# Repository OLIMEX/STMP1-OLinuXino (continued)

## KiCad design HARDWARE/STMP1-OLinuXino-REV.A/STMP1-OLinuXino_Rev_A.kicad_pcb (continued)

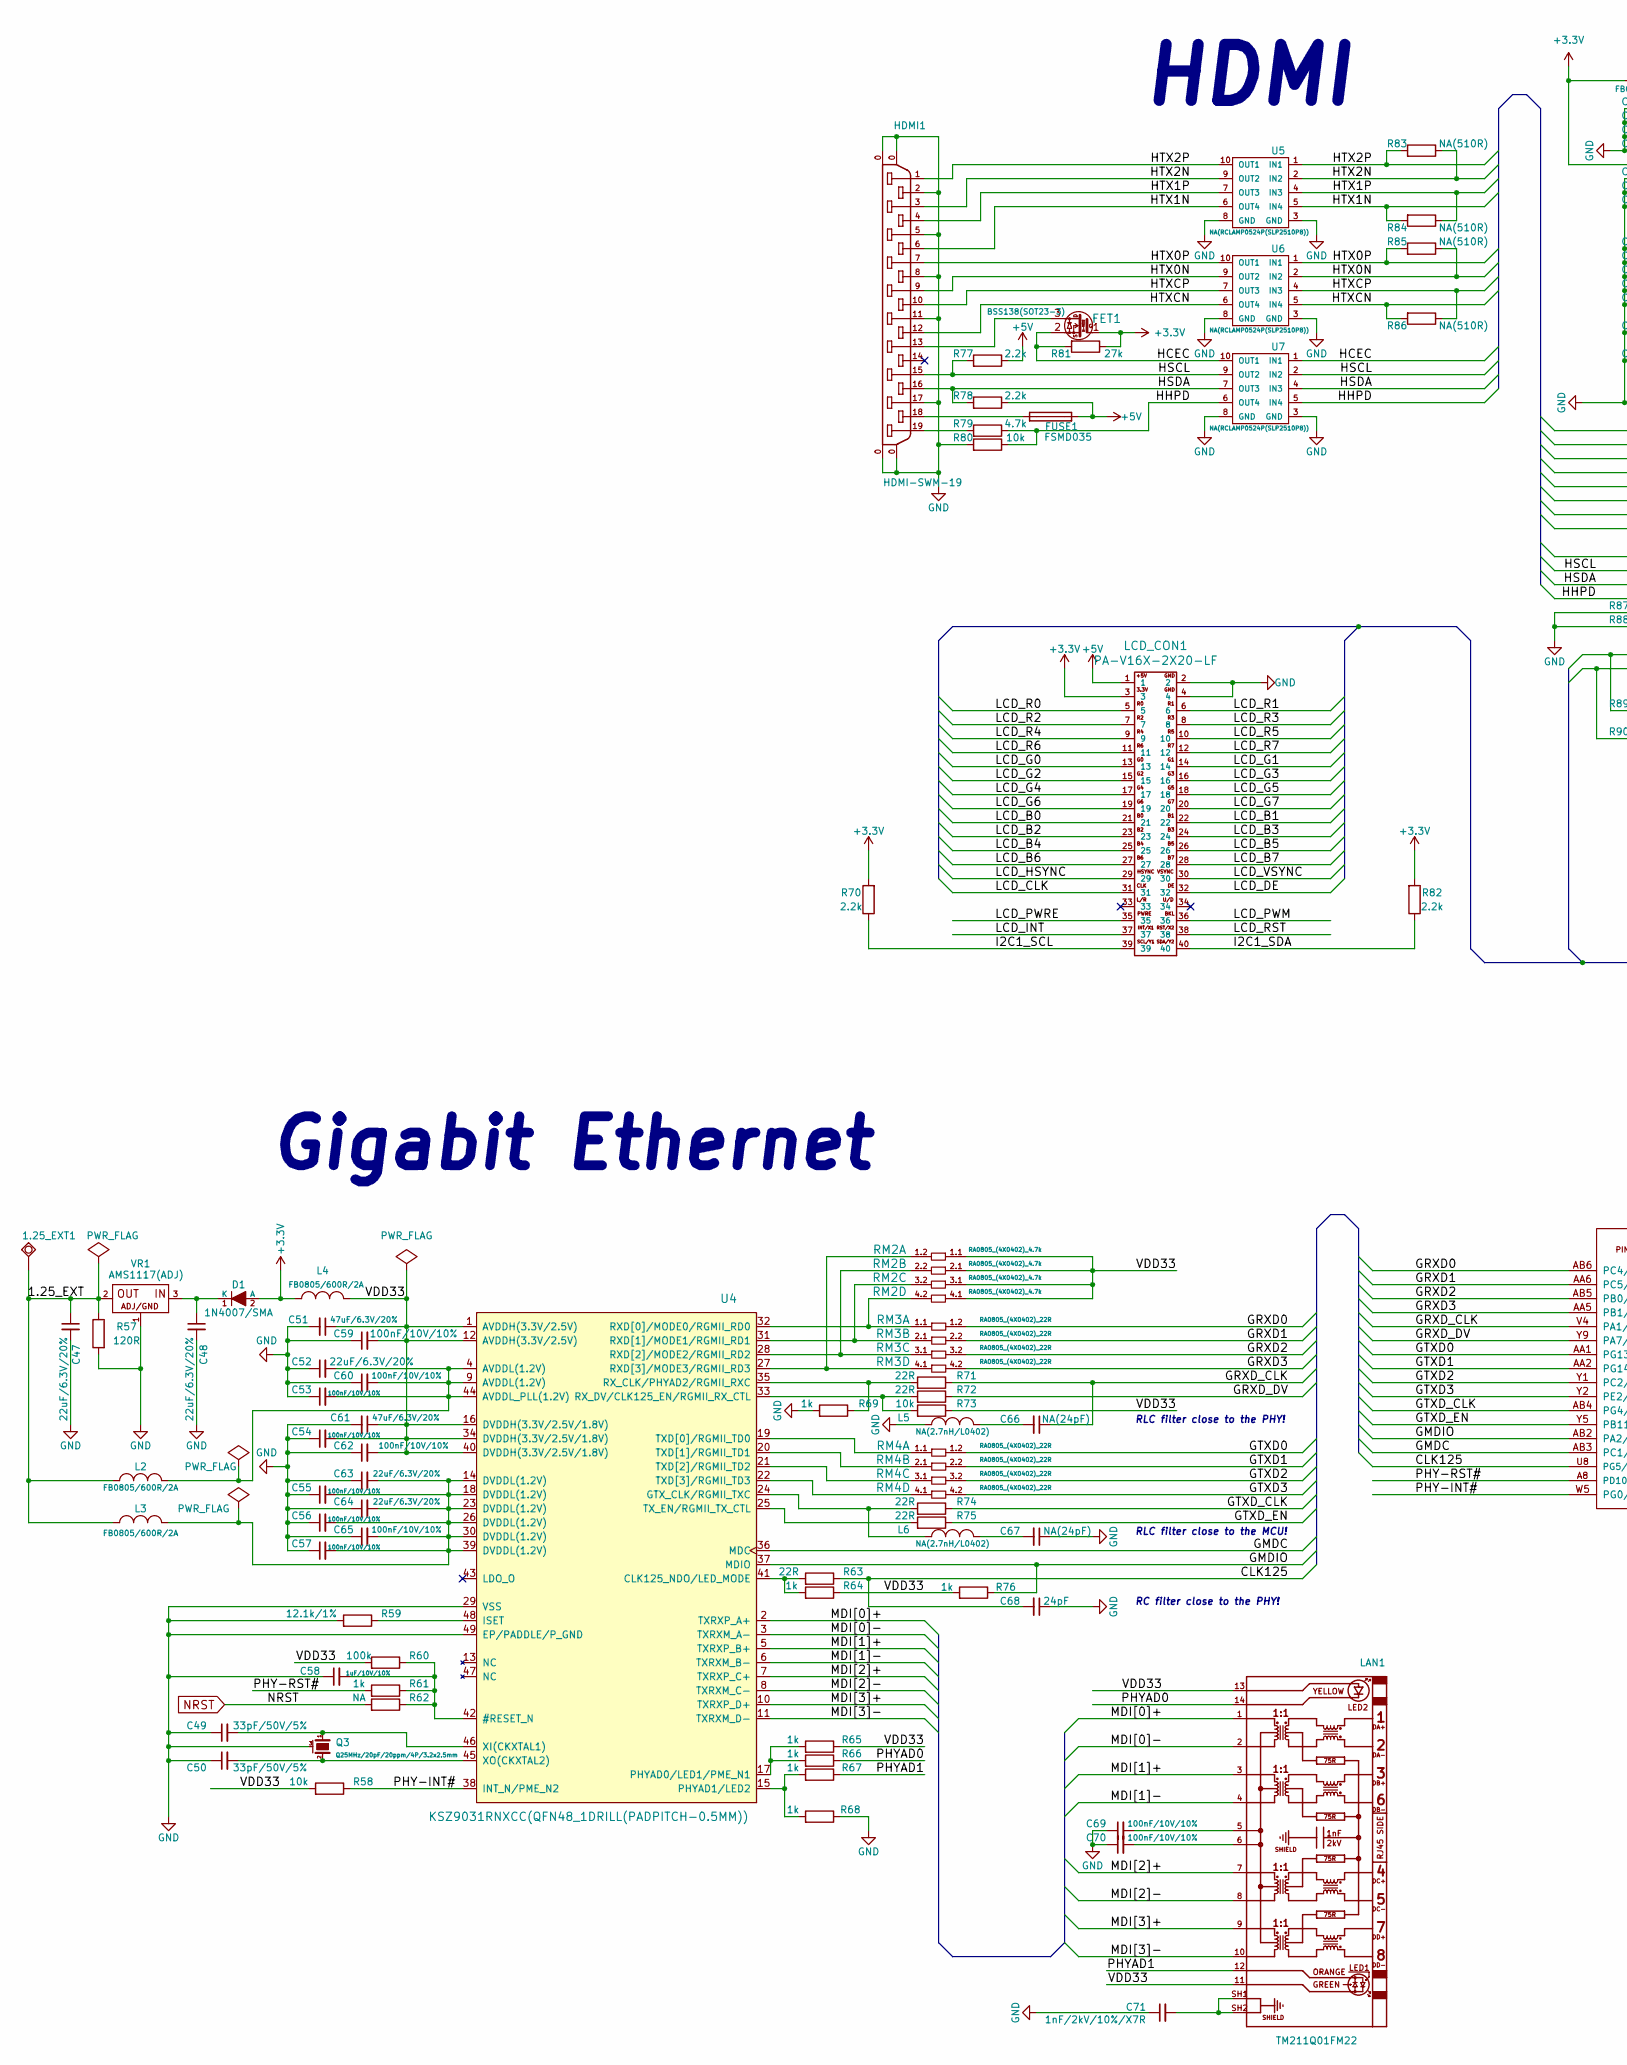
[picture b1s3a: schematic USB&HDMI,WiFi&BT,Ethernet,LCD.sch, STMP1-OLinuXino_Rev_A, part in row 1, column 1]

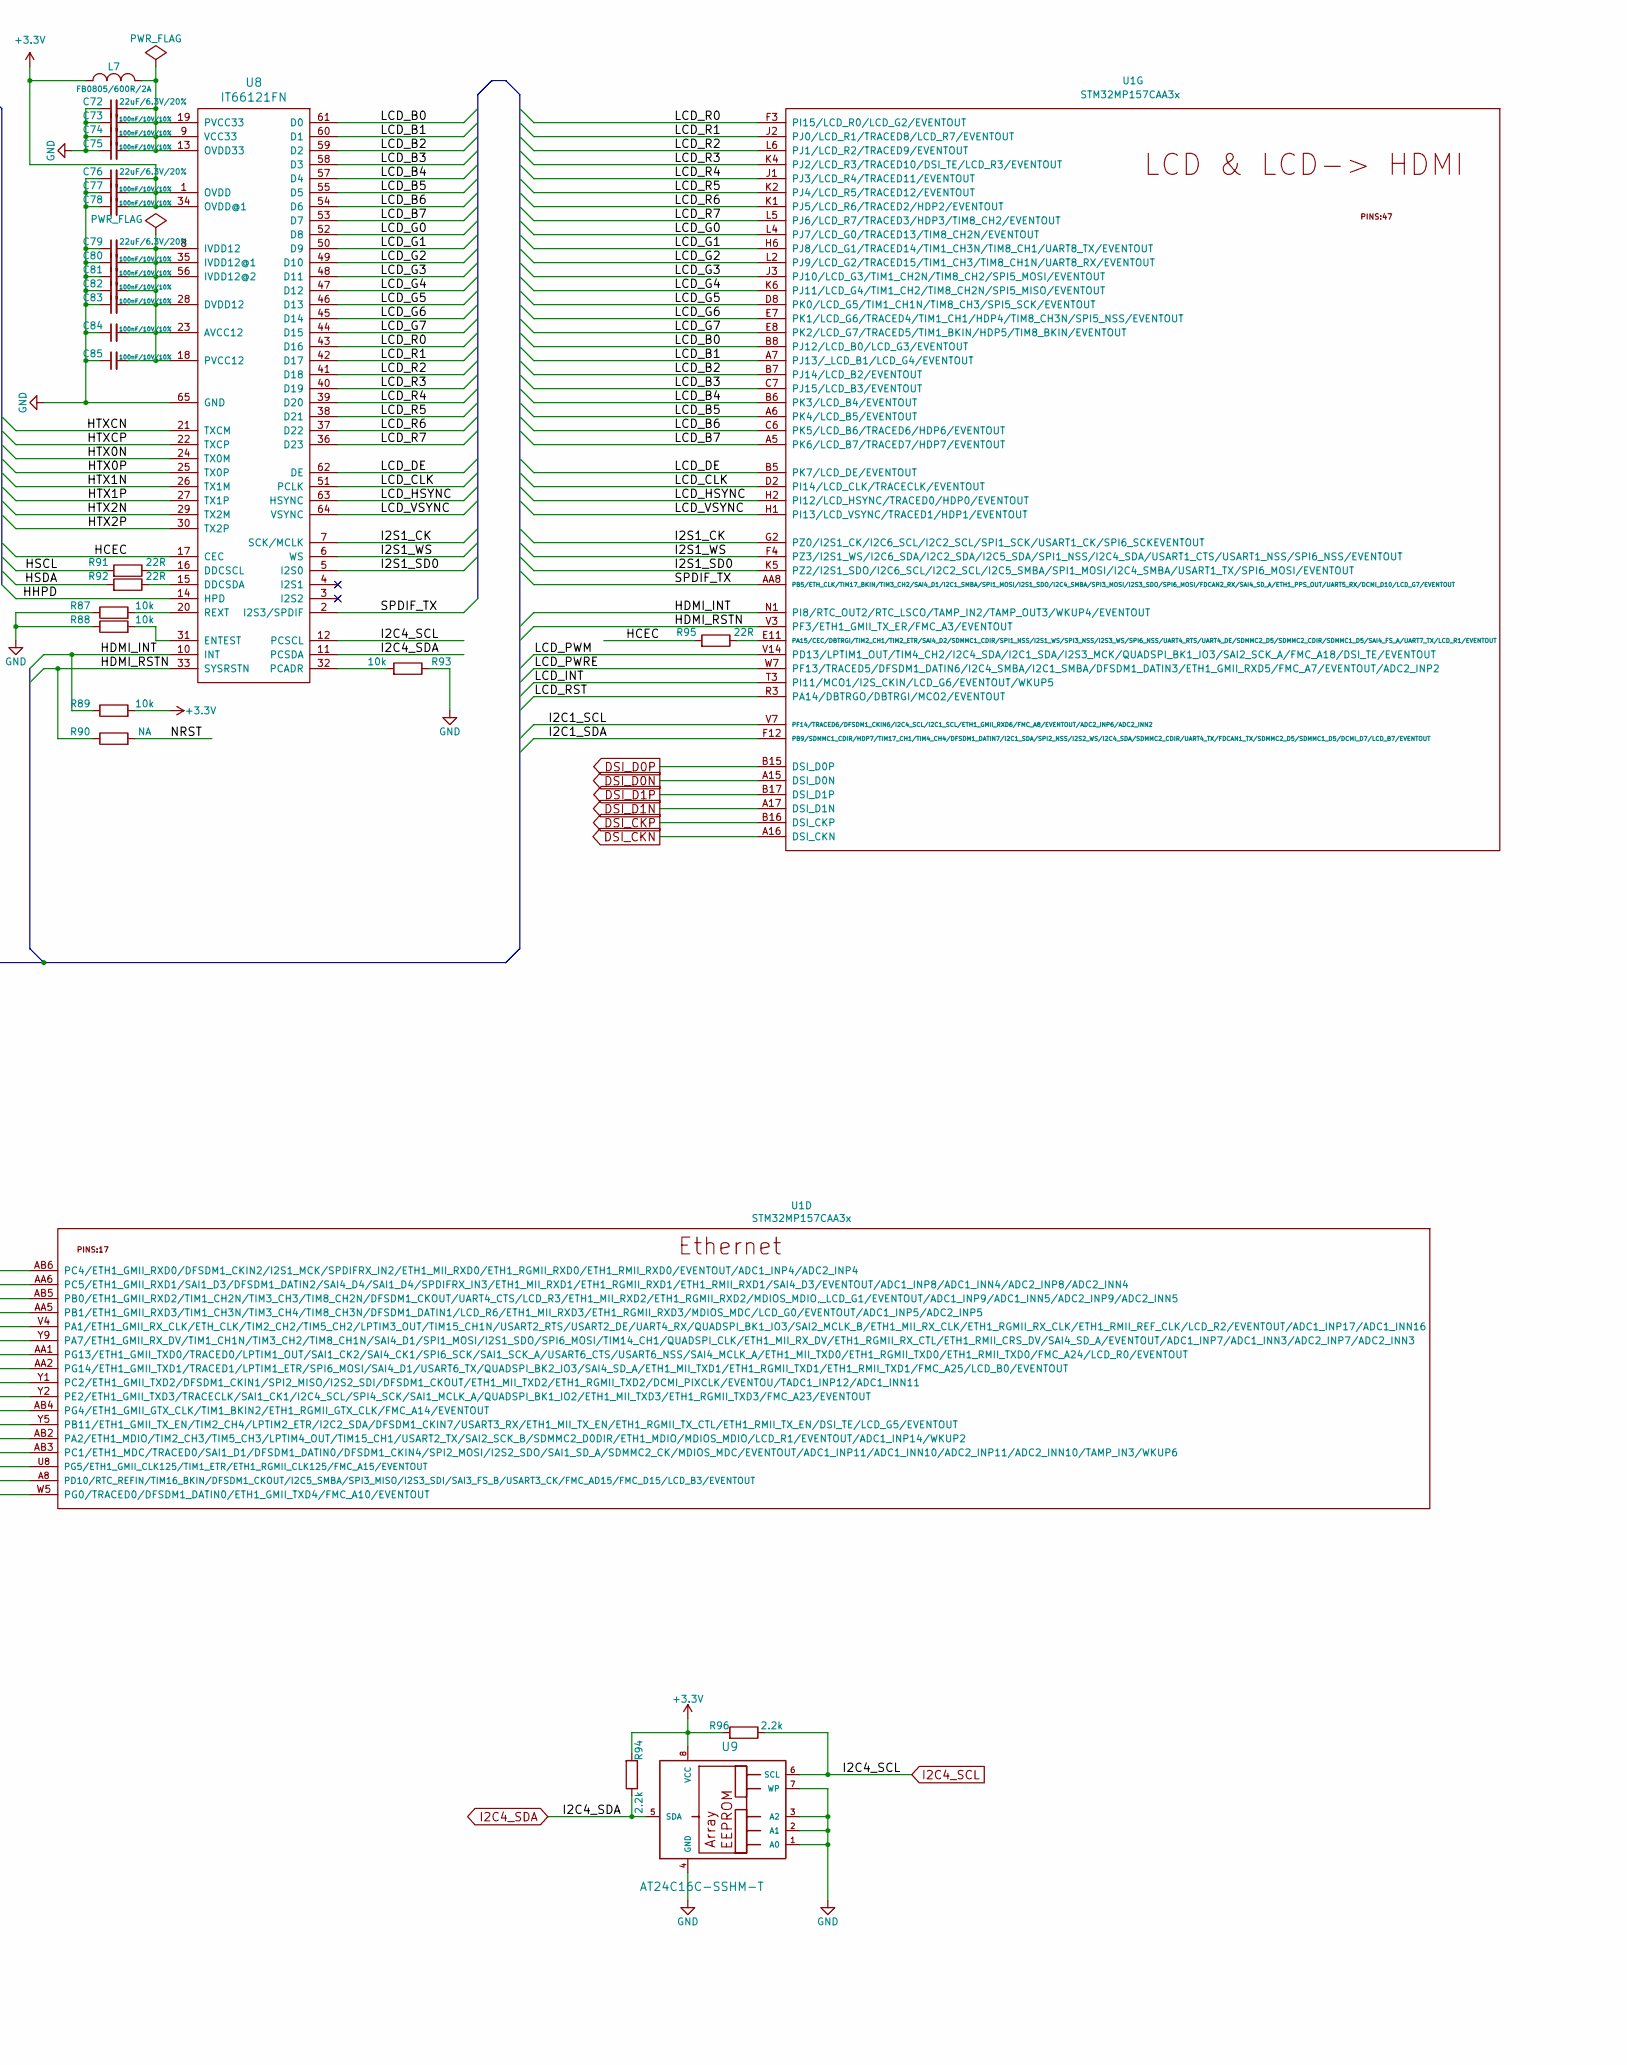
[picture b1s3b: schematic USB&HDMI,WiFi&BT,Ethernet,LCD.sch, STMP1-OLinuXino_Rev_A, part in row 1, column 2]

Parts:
1.25_EXT1: TESTPAD; TP_SMD
C47, C48, C52, C63, C64, C72, C76, C79: 22uF/6.3V/20%; C_0603_5MIL_DWS
C49, C50: 33pF/50V/5%; C_0402_5MIL_DWS
C51, C61: 47uF/6.3V/20%; C_0805_5MIL_DWS
C53, C54, C55, C56, C57, C59, C60, C62, C65, C69, C70, C73, C74, C75, C77, C78, C80, C81, C82, C83, C84, C85: 100nF/10V/10%; C_0402_5MIL_DWS
C58: 1uF/10V/10%; C_0603_5MIL_DWS
C66, C67: NA(24pF); C_0402_5MIL_DWS
C68: 24pF; C_0402_5MIL_DWS
C71: 1nF/2kV/10%/X7R; C_1206_5MIL_DWS_ISO
D1: 1N4007/SMA; SMA-KA
FET1: BSS138(SOT23-3); SOT23
FUSE1: FSMD035; FUSE-1206
HDMI1: HDMI-SWM-19
L2, L3, L4, L7: FB0805/600R/2A; L_0805_5MIL_DWS
L5, L6: NA(2.7nH/L0402); L_0402_5MIL_DWS
LAN1: TM211Q01FM22
LCD_CON1: PA-V16X-2X20-LF; GPH127SMT-02X20(PA-V16X-2X20-LF)
Q3: Q25MHz/20pF/20ppm/4P/3.2x2.5mm; TSX-3.2x2.5mm_GND(3)
R57: 120R; R_0603_5MIL_DWS
R58, R73, R80, R87, R88, R89, R93: 10k; R_0402_5MIL_DWS
R59: 12.1k/1%; R_0603_5MIL_DWS
R60: 100k; R_0402_5MIL_DWS
R61, R64, R65, R66, R67, R68, R69, R76: 1k; R_0402_5MIL_DWS
R62, R90: NA; R_0402_5MIL_DWS
R63, R71, R72, R74, R75, R91, R92, R95: 22R; R_0402_5MIL_DWS
R70, R77, R78, R82, R94, R96: 2.2k; R_0402_5MIL_DWS
R79: 4.7k; R_0402_5MIL_DWS
R81: 27k; R_0402_5MIL_DWS
R83, R84, R85, R86: NA(510R); R_0402_5MIL_DWS
RM2: RA0805_(4X0402)_4.7k; RA0805_(4X0402)_xx_BIGGEROUTPADS
RM3, RM4: RA0805_(4X0402)_22R; RA0805_(4X0402)_xx_BIGGEROUTPADS
U1: STM32MP157CAA3x; LFBGA-448(Pitch-0.8mm_Pad-0.4mm_18x18x1.27mm)
U4: KSZ9031RNXCC(QFN48_1DRILL(PADPITCH-0.5MM)); QFN48_1DRILL(PADPITCH-0.5MM)
U5, U6, U7: NA(RCLAMP0524P(SLP2510P8)); SLP2510P8_TEST
U8: IT66121FN; QFN64_9x9mm_Pitch_0.5mm_65PAD_4.5mm
U9: AT24C16C-SSHM-T; SOIC-8_150mil
VR1: AMS1117(ADJ); SOT223

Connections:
+3V3: C76.2, C77.2, C78.2, D1.2 (A), FET1.1 (G), L4.2, L7.2, LCD_CON1.3, R70.2, R81.1, R82.2, R89.2, R94.2, R96.2, U8.1 (OVDD), U8.34 (OVDD@1), U9.8 (VCC); also elsewhere on the board
+5V: FUSE1.1, LCD_CON1.1, R77.1, R78.1; also elsewhere on the board
/USB&HDMI,WiFi&BT,Ethernet,LCD/1.25_EXT: 1.25_EXT1.1, C47.1, L2.2, L3.2, R57.1, VR1.2 (OUT)
/USB&HDMI,WiFi&BT,Ethernet,LCD/CLK125: C68.2, R63.1, U1.U8 (PG5/ETH1_GMII_CLK125/TIM1_ETR/ETH1_RGMI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)
/USB&HDMI,WiFi&BT,Ethernet,LCD/GMDC: U1.AB3 (PC1/ETH1_MDC/TRACED0/SAI1_D1/DFSDM1_DAT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), U4.36 (MDC)
/USB&HDMI,WiFi&BT,Ethernet,LCD/GMDIO: R76.1, U1.AB2 (PA2/ETH1_MDIO/TIM2_CH3/TIM5_CH3/LPTIM4_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), U4.37 (MDIO)
/USB&HDMI,WiFi&BT,Ethernet,LCD/GRXD0: RM3.1.2, U1.AB6 (PC4/ETH1_GMII_RXD0/DFSDM1_CKIN2/I2S1_MC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)
/USB&HDMI,WiFi&BT,Ethernet,LCD/GRXD1: RM3.2.2, U1.AA6 (PC5/ETH1_GMII_RXD1/SAI1_D3/DFSDM1_DATIN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)
/USB&HDMI,WiFi&BT,Ethernet,LCD/GRXD2: RM3.3.2, U1.AB5 (PB0/ETH1_GMII_RXD2/TIM1_CH2N/TIM3_CH3/T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)
/USB&HDMI,WiFi&BT,Ethernet,LCD/GRXD3: RM3.4.2, U1.AA5 (PB1/ETH1_GMII_RXD3/TIM1_CH3N/TIM3_CH4/T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)
/USB&HDMI,WiFi&BT,Ethernet,LCD/GRXD_CLK: C66.1, R71.1, U1.V4 (PA1/ETH1_GMII_RX_CLK/ETH_CLK/ТIM2_CH2/T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)
/USB&HDMI,WiFi&BT,Ethernet,LCD/GRXD_DV: R72.1, U1.Y9 (PA7/ETH1_GMII_RX_DV/TIM1_CH1N/TIM3_CH2/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)
/USB&HDMI,WiFi&BT,Ethernet,LCD/GTXD0: RM4.1.2, U1.AA1 (PG13/ETH1_GMII_TXD0/TRACED0/LPTIM1_OUT/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)
/USB&HDMI,WiFi&BT,Ethernet,LCD/GTXD1: RM4.2.2, U1.AA2 (PG14/ETH1_GMII_TXD1/TRACED1/LPTIM1_ETR/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)
/USB&HDMI,WiFi&BT,Ethernet,LCD/GTXD2: RM4.3.2, U1.Y1 (PC2/ETH1_GMII_TXD2/DFSDM1_CKIN1/SPI2_MI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)
/USB&HDMI,WiFi&BT,Ethernet,LCD/GTXD3: RM4.4.2, U1.Y2 (PE2/ETH1_GMII_TXD3/TRACECLK/SAI1_CK1/I2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)
/USB&HDMI,WiFi&BT,Ethernet,LCD/GTXD_CLK: R74.1, U1.AB4 (PG4/ETH1_GMII_GTX_CLK/TIM1_BKIN2/ETH1_R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)
/USB&HDMI,WiFi&BT,Ethernet,LCD/GTXD_EN: R75.1, U1.Y5 (PB11/ETH1_GMII_TX_EN/TIM2_CH4/LPTIM2_ET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)
/USB&HDMI,WiFi&BT,Ethernet,LCD/HCEC: FET1.2 (S), R81.2, R95.2, U7.1 (IN1), U7.10 (OUT1), U8.17 (CEC)
/USB&HDMI,WiFi&BT,Ethernet,LCD/HDMI_INT: R89.1, U1.N1 (PI8/RTC_OUT2/RTC_LSCO/TAMP_IN2/TAMP_OUT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), U8.10 (INT)
/USB&HDMI,WiFi&BT,Ethernet,LCD/HDMI_RSTN: R90.1, U1.V3 (PF3/ETH1_GMII_TX_ER/FMC_A3/EVENTOUT), U8.33 (SYSRSTN)
/USB&HDMI,WiFi&BT,Ethernet,LCD/HHPD: R79.1, R80.1, U7.5 (IN4), U7.6 (OUT4), U8.14 (HPD)
/USB&HDMI,WiFi&BT,Ethernet,LCD/HSCL: HDMI1.15, R77.2, R91.2, U7.2 (IN2), U7.9 (OUT2)
/USB&HDMI,WiFi&BT,Ethernet,LCD/HSDA: HDMI1.16, R78.2, R92.2, U7.4 (IN3), U7.7 (OUT3)
/USB&HDMI,WiFi&BT,Ethernet,LCD/HTX0N: HDMI1.9, R85.1, U6.2 (IN2), U6.9 (OUT2), U8.24 (TX0M)
/USB&HDMI,WiFi&BT,Ethernet,LCD/HTX0P: HDMI1.7, R85.2, U6.1 (IN1), U6.10 (OUT1), U8.25 (TX0P)
/USB&HDMI,WiFi&BT,Ethernet,LCD/HTX1N: HDMI1.6, R84.2, U5.5 (IN4), U5.6 (OUT4), U8.26 (TX1M)
/USB&HDMI,WiFi&BT,Ethernet,LCD/HTX1P: HDMI1.4, R84.1, U5.4 (IN3), U5.7 (OUT3), U8.27 (TX1P)
/USB&HDMI,WiFi&BT,Ethernet,LCD/HTX2N: HDMI1.3, R83.1, U5.2 (IN2), U5.9 (OUT2), U8.29 (TX2M)
/USB&HDMI,WiFi&BT,Ethernet,LCD/HTX2P: HDMI1.1, R83.2, U5.1 (IN1), U5.10 (OUT1), U8.30 (TX2P)
/USB&HDMI,WiFi&BT,Ethernet,LCD/HTXCN: HDMI1.12, R86.2, U6.5 (IN4), U6.6 (OUT4), U8.21 (TXCM)
/USB&HDMI,WiFi&BT,Ethernet,LCD/HTXCP: HDMI1.10, R86.1, U6.4 (IN3), U6.7 (OUT3), U8.22 (TXCP)
/USB&HDMI,WiFi&BT,Ethernet,LCD/I2C1_SCL: LCD_CON1.39, R70.1, U1.V7 (PF14/TRACED6/DFSDM1_CKIN6/I2C4_SCL/I2C1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)
/USB&HDMI,WiFi&BT,Ethernet,LCD/I2C1_SDA: LCD_CON1.40, R82.1, U1.F12 (PB9/SDMMC1_CDIR/HDP7/TIM17_CH1/TIM4_CH4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)
/USB&HDMI,WiFi&BT,Ethernet,LCD/I2S1_CK: U1.G2 (PZ0/I2S1_CK/I2C6_SCL/I2C2_SCL/SPI1_SCK/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), U8.7 (SCK/MCLK)
/USB&HDMI,WiFi&BT,Ethernet,LCD/I2S1_SD0: U1.K5 (PZ2/I2S1_SDO/I2C6_SCL/I2C2_SCL/I2C5_SMB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), U8.5 (I2S0)
/USB&HDMI,WiFi&BT,Ethernet,LCD/I2S1_WS: U1.F4 (PZ3/I2S1_WS/I2C6_SDA/I2C2_SDA/I2C5_SDA/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), U8.6 (WS)
/USB&HDMI,WiFi&BT,Ethernet,LCD/LCD_B0: LCD_CON1.21, U1.B8 (PJ12/LCD_B0/LCD_G3/EVENTOUT), U8.61 (D0)
/USB&HDMI,WiFi&BT,Ethernet,LCD/LCD_B1: LCD_CON1.22, U1.A7 (PJ13/_LCD_B1/LCD_G4/EVENTOUT), U8.60 (D1)
/USB&HDMI,WiFi&BT,Ethernet,LCD/LCD_B2: LCD_CON1.23, U1.B7 (PJ14/LCD_B2/EVENTOUT), U8.59 (D2)
/USB&HDMI,WiFi&BT,Ethernet,LCD/LCD_B3: LCD_CON1.24, U1.C7 (PJ15/LCD_B3/EVENTOUT), U8.58 (D3)
/USB&HDMI,WiFi&BT,Ethernet,LCD/LCD_B4: LCD_CON1.25, U1.B6 (PK3/LCD_B4/EVENTOUT), U8.57 (D4)
/USB&HDMI,WiFi&BT,Ethernet,LCD/LCD_B5: LCD_CON1.26, U1.A6 (PK4/LCD_B5/EVENTOUT), U8.55 (D5)
/USB&HDMI,WiFi&BT,Ethernet,LCD/LCD_B6: LCD_CON1.27, U1.C6 (PK5/LCD_B6/TRACED6/HDP6/EVENTOUT), U8.54 (D6)
/USB&HDMI,WiFi&BT,Ethernet,LCD/LCD_B7: LCD_CON1.28, U1.A5 (PK6/LCD_B7/TRACED7/HDP7/EVENTOUT), U8.53 (D7)
/USB&HDMI,WiFi&BT,Ethernet,LCD/LCD_CLK: LCD_CON1.31, U1.D2 (PI14/LCD_CLK/TRACECLK/EVENTOUT), U8.51 (PCLK)
/USB&HDMI,WiFi&BT,Ethernet,LCD/LCD_DE: LCD_CON1.32, U1.B5 (PK7/LCD_DE/EVENTOUT), U8.62 (DE)
/USB&HDMI,WiFi&BT,Ethernet,LCD/LCD_G0: LCD_CON1.13, U1.L4 (PJ7/LCD_G0/TRACED13/TIM8_CH2N/EVENTOUT), U8.52 (D8)
/USB&HDMI,WiFi&BT,Ethernet,LCD/LCD_G1: LCD_CON1.14, U1.H6 (PJ8/LCD_G1/TRACED14/TIM1_CH3N/TIM8_CH1/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), U8.50 (D9)
/USB&HDMI,WiFi&BT,Ethernet,LCD/LCD_G2: LCD_CON1.15, U1.L2 (PJ9/LCD_G2/TRACED15/TIM1_CH3/TIM8_CH1N/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), U8.49 (D10)
/USB&HDMI,WiFi&BT,Ethernet,LCD/LCD_G3: LCD_CON1.16, U1.J3 (PJ10/LCD_G3/TIM1_CH2N/TIM8_CH2/SPI5_MOS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), U8.48 (D11)
/USB&HDMI,WiFi&BT,Ethernet,LCD/LCD_G4: LCD_CON1.17, U1.K6 (PJ11/LCD_G4/TIM1_CH2/TIM8_CH2N/SPI5_MIS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), U8.47 (D12)
/USB&HDMI,WiFi&BT,Ethernet,LCD/LCD_G5: LCD_CON1.18, U1.D8 (PK0/LCD_G5/TIM1_CH1N/TIM8_CH3/SPI5_SCK/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), U8.46 (D13)
/USB&HDMI,WiFi&BT,Ethernet,LCD/LCD_G6: LCD_CON1.19, U1.E7 (PK1/LCD_G6/TRACED4/TIM1_CH1/HDP4/TIM8_C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), U8.45 (D14)
/USB&HDMI,WiFi&BT,Ethernet,LCD/LCD_G7: LCD_CON1.20, U1.E8 (PK2/LCD_G7/TRACED5/TIM1_BKIN/HDP5/TIM8_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), U8.44 (D15)
/USB&HDMI,WiFi&BT,Ethernet,LCD/LCD_HSYNC: LCD_CON1.29, U1.H2 (PI12/LCD_HSYNC/TRACED0/HDP0/EVENTOUT), U8.63 (HSYNC)
/USB&HDMI,WiFi&BT,Ethernet,LCD/LCD_INT: LCD_CON1.37, U1.T3 (PI11/MCO1/I2S_CKIN/LCD_G6/EVENTOUT/WKUP5)
/USB&HDMI,WiFi&BT,Ethernet,LCD/LCD_PWM: LCD_CON1.36, U1.V14 (PD13/LPTIM1_OUT/TIM4_CH2/I2C4_SDA/I2C1_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)
/USB&HDMI,WiFi&BT,Ethernet,LCD/LCD_PWRE: LCD_CON1.35, U1.W7 (PF13/TRACED5/DFSDM1_DATIN6/I2C4_SMBA/I2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)
/USB&HDMI,WiFi&BT,Ethernet,LCD/LCD_R0: LCD_CON1.5, U1.F3 (PI15/LCD_R0/LCD_G2/EVENTOUT), U8.43 (D16)
/USB&HDMI,WiFi&BT,Ethernet,LCD/LCD_R1: LCD_CON1.6, U1.J2 (PJ0/LCD_R1/TRACED8/LCD_R7/EVENTOUT), U8.42 (D17)
/USB&HDMI,WiFi&BT,Ethernet,LCD/LCD_R2: LCD_CON1.7, U1.L6 (PJ1/LCD_R2/TRACED9/EVENTOUT), U8.41 (D18)
/USB&HDMI,WiFi&BT,Ethernet,LCD/LCD_R3: LCD_CON1.8, U1.K4 (PJ2/LCD_R3/TRACED10/DSI_TE/LCD_R3/EVENT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), U8.40 (D19)
/USB&HDMI,WiFi&BT,Ethernet,LCD/LCD_R4: LCD_CON1.9, U1.J1 (PJ3/LCD_R4/TRACED11/EVENTOUT), U8.39 (D20)
/USB&HDMI,WiFi&BT,Ethernet,LCD/LCD_R5: LCD_CON1.10, U1.K2 (PJ4/LCD_R5/TRACED12/EVENTOUT), U8.38 (D21)
/USB&HDMI,WiFi&BT,Ethernet,LCD/LCD_R6: LCD_CON1.11, U1.K1 (PJ5/LCD_R6/TRACED2/HDP2/EVENTOUT), U8.37 (D22)
/USB&HDMI,WiFi&BT,Ethernet,LCD/LCD_R7: LCD_CON1.12, U1.L5 (PJ6/LCD_R7/TRACED3/HDP3/TIM8_CH2/EVENTO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), U8.36 (D23)
/USB&HDMI,WiFi&BT,Ethernet,LCD/LCD_RST: LCD_CON1.38, U1.R3 (PA14/DBTRGO/DBTRGI/MCO2/EVENTOUT)
/USB&HDMI,WiFi&BT,Ethernet,LCD/LCD_VSYNC: LCD_CON1.30, U1.H1 (PI13/LCD_VSYNC/TRACED1/HDP1/EVENTOUT), U8.64 (VSYNC)
/USB&HDMI,WiFi&BT,Ethernet,LCD/MDI[0]+: LAN1.1, U4.2 (TXRXP_A+)
/USB&HDMI,WiFi&BT,Ethernet,LCD/MDI[0]-: LAN1.2, U4.3 (TXRXM_A-)
/USB&HDMI,WiFi&BT,Ethernet,LCD/MDI[1]+: LAN1.3, U4.5 (TXRXP_B+)
/USB&HDMI,WiFi&BT,Ethernet,LCD/MDI[1]-: LAN1.4, U4.6 (TXRXM_B-)
/USB&HDMI,WiFi&BT,Ethernet,LCD/MDI[2]+: LAN1.7, U4.7 (TXRXP_C+)
/USB&HDMI,WiFi&BT,Ethernet,LCD/MDI[2]-: LAN1.8, U4.8 (TXRXM_C-)
/USB&HDMI,WiFi&BT,Ethernet,LCD/MDI[3]+: LAN1.9, U4.10 (TXRXP_D+)
/USB&HDMI,WiFi&BT,Ethernet,LCD/MDI[3]-: LAN1.10, U4.11 (TXRXM_D-)
/USB&HDMI,WiFi&BT,Ethernet,LCD/PHY-INT#: R58.1, U1.W5 (PG0/TRACED0/DFSDM1_DATIN0/ETH1_GMII_TXD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), U4.38 (INT_N/PME_N2)
/USB&HDMI,WiFi&BT,Ethernet,LCD/PHY-RST#: R61.2, U1.A8 (PD10/RTC_REFIN/TIM16_BKIN/DFSDM1_CKOUT/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)
/USB&HDMI,WiFi&BT,Ethernet,LCD/PHYAD0: LAN1.14, R66.1
/USB&HDMI,WiFi&BT,Ethernet,LCD/PHYAD1: LAN1.12, R67.1
/USB&HDMI,WiFi&BT,Ethernet,LCD/SPDIF_TX: U1.AA8 (PB5/ETH_CLK/TIM17_BKIN/TIM3_CH2/SAI4_D1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), U8.2 (I2S3/SPDIF)
/USB&HDMI,WiFi&BT,Ethernet,LCD/VDD33: C51.1, C54.2, C59.2, C61.1, C62.2, L4.1, LAN1.11, LAN1.13, R58.2, R60.2, R64.1, R65.1, R73.1, R76.2, RM2.1.1, RM2.2.1, RM2.3.1, RM2.4.1, U4.1 (AVDDH(3.3V/2.5V)), U4.12 (AVDDH(3.3V/2.5V)), U4.16 (DVDDH(3.3V/2.5V/1.8V)), U4.34 (DVDDH(3.3V/2.5V/1.8V)), U4.40 (DVDDH(3.3V/2.5V/1.8V))
DSI_CKN: U1.A16 (DSI_CKN); also elsewhere on the board
DSI_CKP: U1.B16 (DSI_CKP); also elsewhere on the board
DSI_D0N: U1.A15 (DSI_D0N); also elsewhere on the board
DSI_D0P: U1.B15 (DSI_D0P); also elsewhere on the board
DSI_D1N: U1.A17 (DSI_D1N); also elsewhere on the board
DSI_D1P: U1.B17 (DSI_D1P); also elsewhere on the board
GND: C47.2, C48.2, C49.1, C50.1, C51.2, C52.1, C53.1, C54.1, C55.1, C56.1, C57.1, C58.1, C59.1, C60.1, C61.2, C62.1, C63.1, C64.1, C65.1, C67.1, C68.1, C69.1, C70.1, C71.1, C72.1, C73.1, C74.1, C75.1, C76.1, C77.1, C78.1, C79.1, C80.1, C81.1, C82.1, C83.1, C84.1, C85.1, HDMI1.0 (20), HDMI1.2, HDMI1.5, HDMI1.8, HDMI1.11, HDMI1.17, L5.2, LCD_CON1.2, LCD_CON1.4, Q3.3 (case), R57.2, R59.2, R68.1, R69.2, R80.2, R87.1, R88.1, R93.1, U4.29 (VSS), U4.49 (EP/PADDLE/P_GND), U5.3 (GND), U5.8 (GND), U6.3 (GND), U6.8 (GND), U7.3 (GND), U7.8 (GND), U8.65 (GND), U9.1 (A0), U9.2 (A1), U9.3 (A2), U9.4 (GND), U9.7 (WP), VR1.1 (ADJ/GND); also elsewhere on the board
I2C4_SCL: R96.1, U8.12 (PCSCL), U9.6 (SCL); also elsewhere on the board
I2C4_SDA: R94.1, U8.11 (PCSDA), U9.5 (SDA); also elsewhere on the board
NRST: R62.2, R90.2; also elsewhere on the board
unnamed: C48.1, D1.1 (K), VR1.3 (IN)
unnamed: C49.2, Q3.1, U4.46 (XI(CKXTAL1))
unnamed: C50.2, Q3.2, U4.45 (XO(CKXTAL2))
unnamed: C52.2, C53.2, C60.2, L2.1, U4.4 (AVDDL(1.2V)), U4.9 (AVDDL(1.2V)), U4.44 (AVDDL_PLL(1.2V))
unnamed: C55.2, C56.2, C57.2, C63.2, C64.2, C65.2, L3.1, U4.14 (DVDDL(1.2V)), U4.18 (DVDDL(1.2V)), U4.23 (DVDDL(1.2V)), U4.26 (DVDDL(1.2V)), U4.30 (DVDDL(1.2V)), U4.39 (DVDDL(1.2V))
unnamed: C58.2, R60.1, R61.1, R62.1, U4.42 (#RESET_N)
unnamed: C66.2, L5.1
unnamed: C67.2, L6.1
unnamed: C69.2, LAN1.5
unnamed: C70.2, LAN1.6
unnamed: C71.2, LAN1.SH1, LAN1.SH2
unnamed: C72.2, C73.2, C74.2, C75.2, L7.1, U8.9 (VCC33), U8.13 (OVDD33), U8.19 (PVCC33)
unnamed: C79.2, C80.2, C81.2, C82.2, C83.2, C84.2, C85.2, U8.8 (IVDD12), U8.18 (PVCC12), U8.23 (AVCC12), U8.28 (DVDD12), U8.35 (IVDD12@1), U8.56 (IVDD12@2)
unnamed: FET1.3 (D), HDMI1.13
unnamed: FUSE1.2, HDMI1.18
unnamed: HDMI1.19, R79.2
unnamed: L6.2, R74.2, U4.24 (GTX_CLK/RGMII_TXC)
unnamed: R59.1, U4.48 (ISET)
unnamed: R63.2, R64.2, U4.41 (CLK125_NDO/LED_MODE)
unnamed: R65.2, R66.2, U4.17 (PHYAD0/LED1/PME_N1)
unnamed: R67.2, R68.2, U4.15 (PHYAD1/LED2)
unnamed: R69.1, R71.2, U4.35 (RX_CLK/PHYAD2/RGMII_RXC)
unnamed: R72.2, R73.2, U4.33 (RX_DV/CLK125_EN/RGMII_RX_CTL)
unnamed: R75.2, U4.25 (TX_EN/RGMII_TX_CTL)
unnamed: R87.2, U8.20 (REXT)
unnamed: R88.2, U8.31 (ENTEST)
unnamed: R91.1, U8.16 (DDCSCL)
unnamed: R92.1, U8.15 (DDCSDA)
unnamed: R93.2, U8.32 (PCADR)
unnamed: R95.1, U1.E11 (PA15/CEC/DBTRGI/TIM2_CH1/TIM2_ETR/SAI4_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)
unnamed: RM2.1.2, RM3.4.1, U4.27 (RXD[3]/MODE3/RGMII_RD3)
unnamed: RM2.2.2, RM3.3.1, U4.28 (RXD[2]/MODE2/RGMII_RD2)
unnamed: RM2.3.2, RM3.2.1, U4.31 (RXD[1]/MODE1/RGMII_RD1)
unnamed: RM2.4.2, RM3.1.1, U4.32 (RXD[0]/MODE0/RGMII_RD0)
unnamed: RM4.1.1, U4.19 (TXD[0]/RGMII_TD0)
unnamed: RM4.2.1, U4.20 (TXD[1]/RGMII_TD1)
unnamed: RM4.3.1, U4.21 (TXD[2]/RGMII_TD2)
unnamed: RM4.4.1, U4.22 (TXD[3]/RGMII_TD3)

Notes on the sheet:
HDMI
Gigabit Ethernet
RLC filter close to the MCU!
RLC filter close to the PHY!
RC filter close to the PHY!

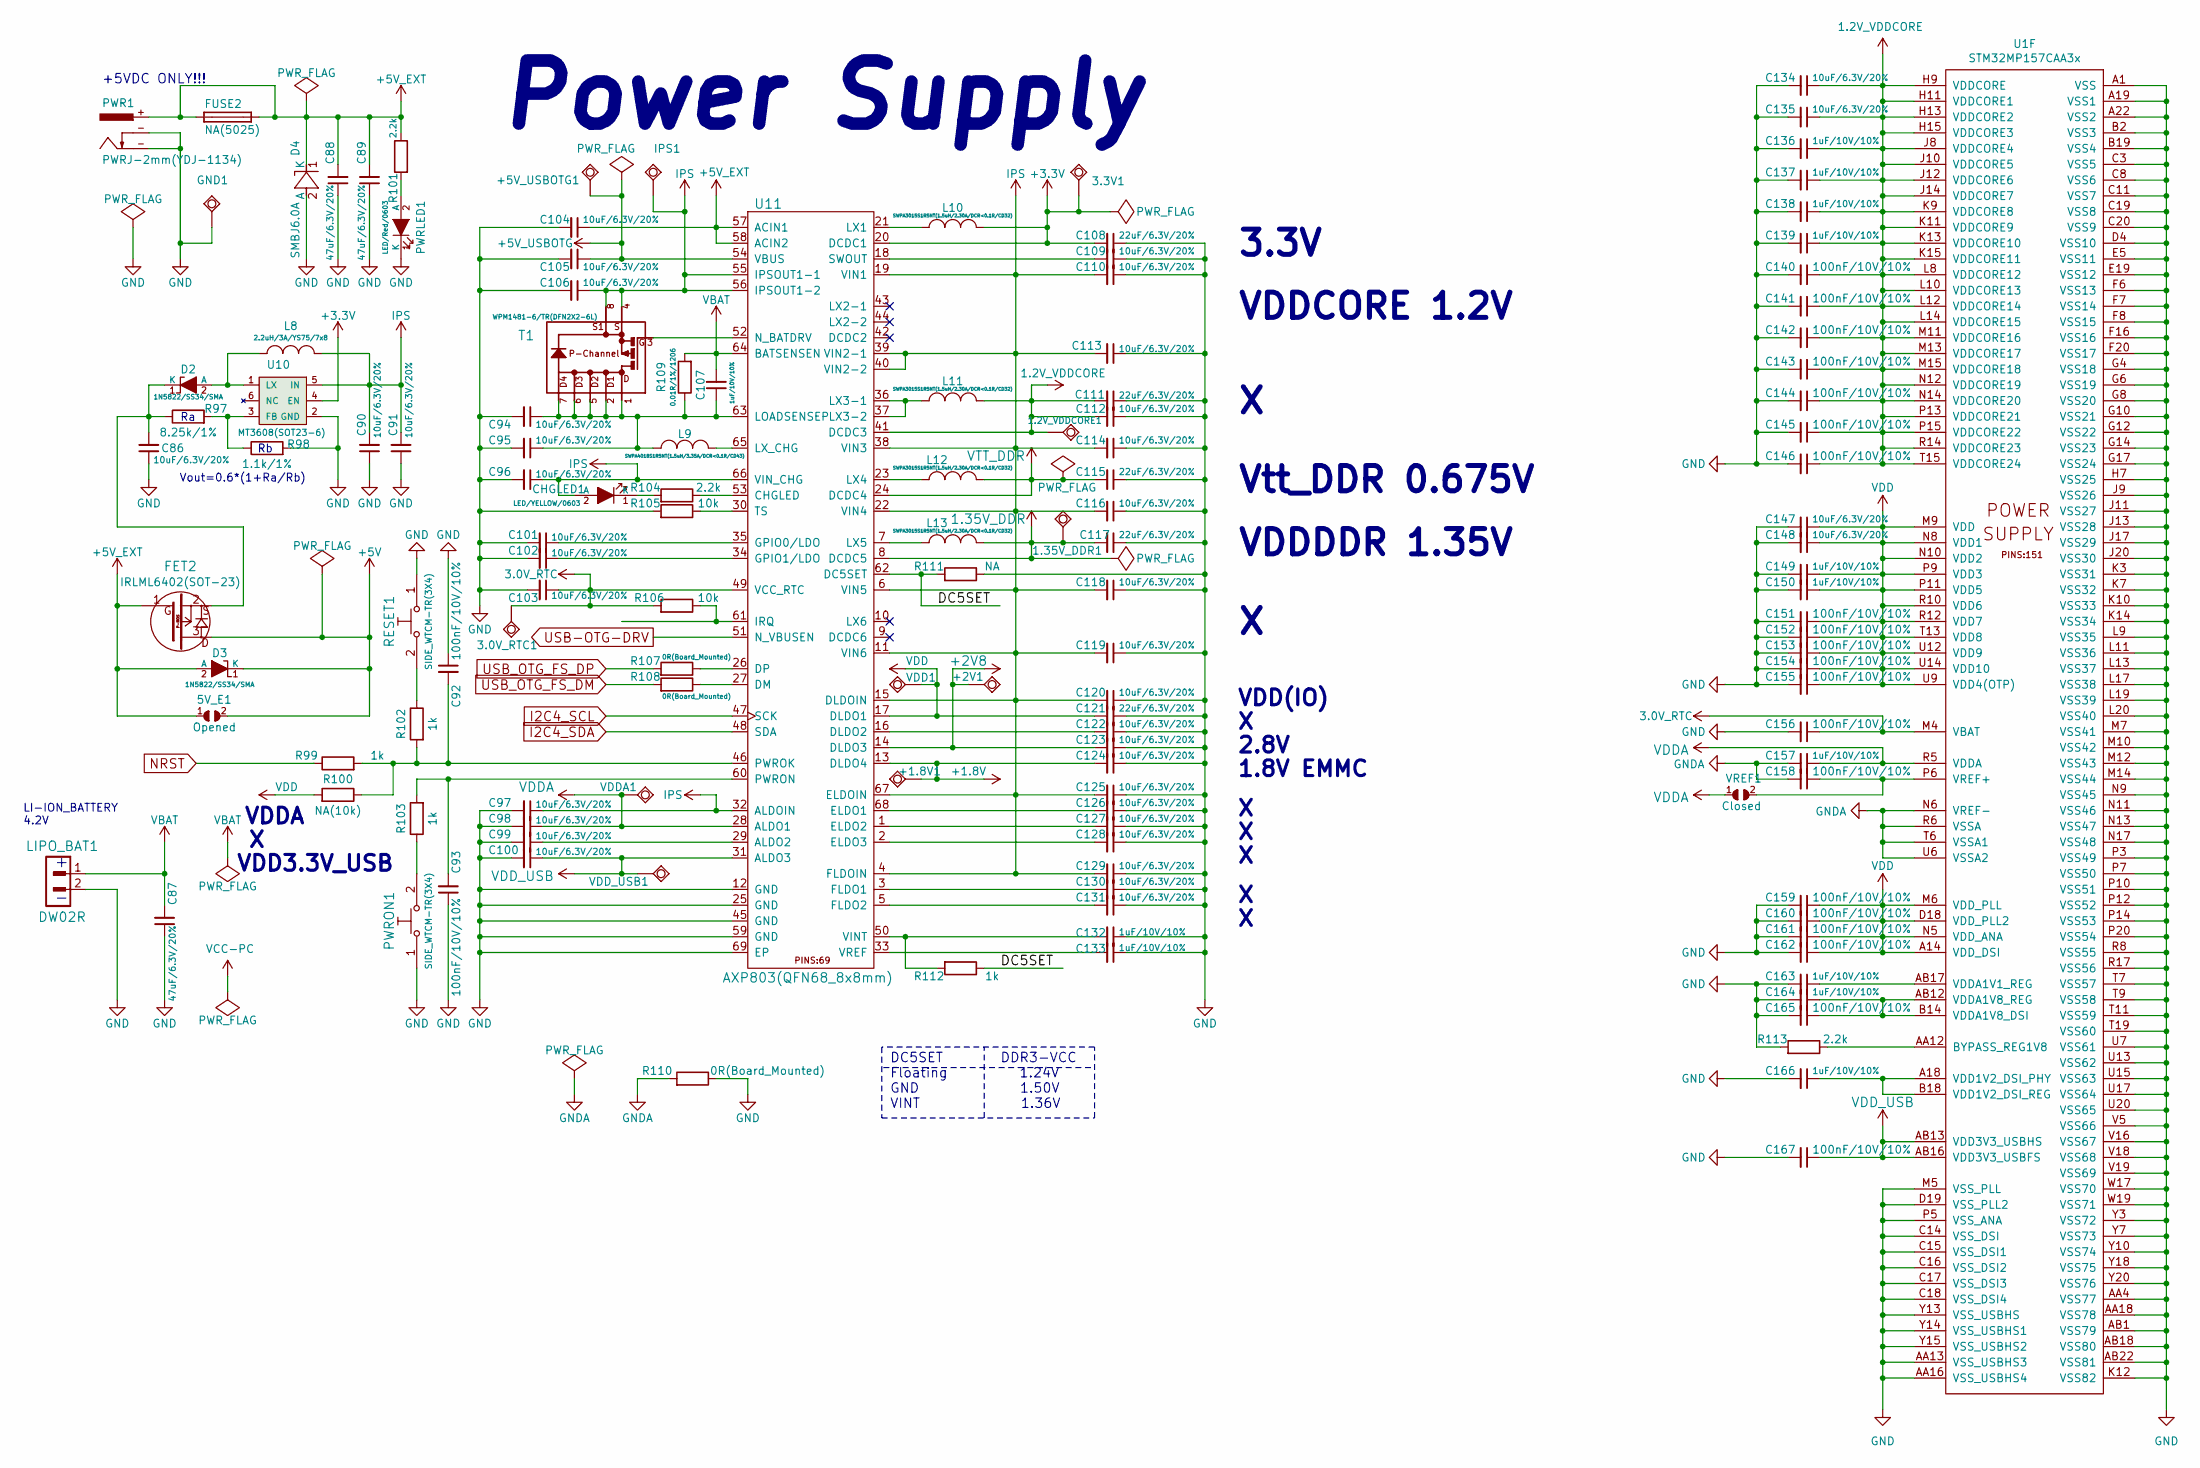
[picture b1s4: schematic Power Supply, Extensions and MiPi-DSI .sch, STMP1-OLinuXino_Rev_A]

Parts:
1.2V_VDDCORE1, 1.35V_DDR1, 3.0V_RTC1, 3.3V1: TESTPAD; TP_SMD
5V_E1: Opened; SJ_1_SMALLER
+1.8V1, +2V1, +5V_USBOTG1: TESTPAD; TP_SMD
C86, C90, C91, C94, C95, C96, C97, C98, C99, C100, C101, C102, C103, C104, C105, C106, C109, C110, C112, C113, C114, C116, C118, C119, C120, C122, C123, C124, C125, C126, C127, C128, C129, C130, C131, C134, C135, C147, C148: 10uF/6.3V/20%; C_0603_5MIL_DWS
C87, C88, C89: 47uF/6.3V/20%; C_0805_5MIL_DWS
C92, C93, C140, C141, C142, C143, C144, C145, C146, C151, C152, C153, C154, C155, C156, C158, C159, C160, C161, C162, C165, C167: 100nF/10V/10%; C_0402_5MIL_DWS
C107, C132, C133, C136, C137, C138, C139, C149, C150, C157, C163, C164, C166: 1uF/10V/10%; C_0603_5MIL_DWS
C108, C111, C115, C117, C121: 22uF/6.3V/20%; C_0603_5MIL_DWS
CHGLED1: LED/YELLOW/0603; LED_0603_KA
D2, D3: 1N5822/SS34/SMA; SMA-KA
D4: SMBJ6.0A; DO214AA_1(K)-2(A)
FET2: IRLML6402(SOT-23); SOT23
FUSE2: NA(5025); FUSE-5025
GND1: TESTPAD; TP_SMD
IPS1: TESTPAD; TP_SMD
L8: 2.2uH/3A/YS75/7x8; YS75_7X8MM
L9: SWPA4018S1R5NT(1.5uH/3.35A/DCR<0.1R/CD43); CD42(43)
L10, L11, L12, L13: SWPA3015S1R5NT(1.5uH/2.30A/DCR<0.1R/CD32); CD32
LIPO_BAT1: DW02R; LIPO_BAT-CON2DW02R
PWR1: PWRJ-2mm(YDJ-1134)
PWRLED1: LED/Red/0603; LED_0603_KA
PWRON1: SIDE_WTCM-TR(3X4); SW-TAKT3X4
R97: 8.25k/1%; R_0402_5MIL_DWS
R98: 1.1k/1%; R_0402_5MIL_DWS
R99, R102, R103, R112: 1k; R_0402_5MIL_DWS
R100: NA(10k); R_0402_5MIL_DWS
R101, R104, R113: 2.2k; R_0402_5MIL_DWS
R105, R106: 10k; R_0402_5MIL_DWS
R107, R108: 0R(Board_Mounted); R_0402_5MIL_0R(Board_Mounted)
R109: 0.01R/1%/1206; R_1206_5MIL_DWS
R110: 0R(Board_Mounted); R_0603_5MIL_0R(Board_Mounted)
R111: NA; R_0402_5MIL_DWS
RESET1: SIDE_WTCM-TR(3X4); SW-TAKT3X4
T1: WPM1481-6/TR(DFN2X2-6L); DFN2x2-6L
U1: STM32MP157CAA3x; LFBGA-448(Pitch-0.8mm_Pad-0.4mm_18x18x1.27mm)
U10: MT3608(SOT23-6); SOT23-6
U11: AXP803(QFN68_8x8mm); QFN68
VDD1: TESTPAD; TP_SMD
VDDA1: TESTPAD; TP_SMD
VDD_USB1: TESTPAD; TP_SMD
VREF1: Closed; SJ_1_SMALLER_TIED

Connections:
1.1V_CPUX: 1.2V_VDDCORE1.1, C111.2, C112.2, C134.1, C135.1, C136.1, C137.1, C138.1, C139.1, C140.1, C141.1, C142.1, C143.1, C144.1, C145.1, C146.1, L11.2, U1.H9 (VDDCORE), U1.H11 (VDDCORE1), U1.H13 (VDDCORE2), U1.H15 (VDDCORE3), U1.J8 (VDDCORE4), U1.J10 (VDDCORE5), U1.J12 (VDDCORE6), U1.J14 (VDDCORE7), U1.K9 (VDDCORE8), U1.K11 (VDDCORE9), U1.K13 (VDDCORE10), U1.K15 (VDDCORE11), U1.L8 (VDDCORE12), U1.L10 (VDDCORE13), U1.L12 (VDDCORE14), U1.L14 (VDDCORE15), U1.M11 (VDDCORE16), U1.M13 (VDDCORE17), U1.M15 (VDDCORE18), U1.N12 (VDDCORE19), U1.N14 (VDDCORE20), U1.P13 (VDDCORE21), U1.P15 (VDDCORE22), U1.R14 (VDDCORE23), U1.T15 (VDDCORE24), U11.41 (DCDC3)
1.35V_DDR: 1.35V_DDR1.1, C117.2, L13.2, U11.8 (DCDC5); also elsewhere on the board
3.0V_RTC: 3.0V_RTC1.1, C103.1, C156.1, R106.2, U1.M4 (VBAT), U11.49 (VCC_RTC)
+2V8: +2V1.1, C123.2, U11.14 (DLDO3); also elsewhere on the board
+3V3: 3.3V1.1, C108.2, L10.2, U10.4 (EN), U11.20 (DCDC1); also elsewhere on the board
+5V: 5V_E1.2, D3.1 (K), FET2.3; also elsewhere on the board
+5V_EXT: 5V_E1.1, C88.2, C89.2, C104.1, D3.2 (A), D4.1 (K), FET2.1, FUSE2.1, FUSE2.2, PWR1.+, R101.1, U11.57 (ACIN1), U11.58 (ACIN2)
+5V_USBOTG: +5V_USBOTG1.1, C105.1, U11.54 (VBUS); also elsewhere on the board
/Power Supply, Extensions and MiPi-DSI/DC5SET: R111.2, R112.1, U11.62 (DC5SET)
GND: C86.1, C87.1, C88.1, C89.1, C90.1, C91.1, C92.1, C93.1, C94.2, C95.2, C96.2, C97.2, C98.2, C99.2, C100.2, C101.2, C102.2, C103.2, C104.2, C105.2, C106.2, C108.1, C109.1, C110.1, C111.1, C112.1, C113.1, C114.1, C115.1, C116.1, C117.1, C118.1, C119.1, C120.1, C121.1, C122.1, C123.1, C124.1, C125.1, C126.1, C127.1, C128.1, C129.1, C130.1, C131.1, C132.1, C133.1, C134.2, C135.2, C136.2, C137.2, C138.2, C139.2, C140.2, C141.2, C142.2, C143.2, C144.2, C145.2, C146.2, C147.2, C148.2, C149.2, C150.2, C151.2, C152.2, C153.2, C154.2, C155.2, C156.2, C159.2, C160.2, C161.2, C162.2, C163.2, C164.2, C165.2, C166.2, C167.2, D4.2 (A), GND1.1, LIPO_BAT1.2, PWR1.-, PWRLED1.1 (K), PWRON1.1, R98.2, R105.2, R110.1, R111.1, R113.2, RESET1.1, U1.A1 (VSS), U1.A19 (VSS1), U1.A22 (VSS2), U1.AA4 (VSS77), U1.AA13 (VSS_USBHS3), U1.AA16 (VSS_USBHS4), U1.AA18 (VSS78), U1.AB1 (VSS79), U1.AB18 (VSS80), U1.AB22 (VSS81), U1.B2 (VSS3), U1.B19 (VSS4), U1.C3 (VSS5), U1.C8 (VSS6), U1.C11 (VSS7), U1.C14 (VSS_DSI), U1.C15 (VSS_DSI1), U1.C16 (VSS_DSI2), U1.C17 (VSS_DSI3), U1.C18 (VSS_DSI4), U1.C19 (VSS8), U1.C20 (VSS9), U1.D4 (VSS10), U1.D19 (VSS_PLL2), U1.E5 (VSS11), U1.E19 (VSS12), U1.F6 (VSS13), U1.F7 (VSS14), U1.F8 (VSS15), U1.F16 (VSS16), U1.F20 (VSS17), U1.G4 (VSS18), U1.G6 (VSS19), U1.G8 (VSS20), U1.G10 (VSS21), U1.G12 (VSS22), U1.G14 (VSS23), U1.G17 (VSS24), U1.H7 (VSS25), U1.J9 (VSS26), U1.J11 (VSS27), U1.J13 (VSS28), U1.J17 (VSS29), U1.J20 (VSS30), U1.K3 (VSS31), U1.K7 (VSS32), U1.K10 (VSS33), U1.K12 (VSS82), U1.K14 (VSS34), U1.L9 (VSS35), U1.L11 (VSS36), U1.L13 (VSS37), U1.L17 (VSS38), U1.L19 (VSS39), U1.L20 (VSS40), U1.M5 (VSS_PLL), U1.M7 (VSS41), U1.M10 (VSS42), U1.M12 (VSS43), U1.M14 (VSS44), U1.N9 (VSS45), U1.N11 (VSS46), U1.N13 (VSS47), U1.N17 (VSS48), U1.P3 (VSS49), U1.P5 (VSS_ANA), U1.P7 (VSS50), U1.P10 (VSS51), U1.P12 (VSS52), U1.P14 (VSS53), U1.P20 (VSS54), U1.R8 (VSS55), U1.R17 (VSS56), U1.T7 (VSS57), U1.T9 (VSS58), U1.T11 (VSS59), U1.T19 (VSS60), U1.U7 (VSS61), U1.U13 (VSS62), U1.U15 (VSS63), U1.U17 (VSS64), U1.U20 (VSS65), U1.V5 (VSS66), U1.V16 (VSS67), U1.V18 (VSS68), U1.V19 (VSS69), U1.W17 (VSS70), U1.W19 (VSS71), U1.Y3 (VSS72), U1.Y7 (VSS73), U1.Y10 (VSS74), U1.Y13 (VSS_USBHS), U1.Y14 (VSS_USBHS1), U1.Y15 (VSS_USBHS2), U1.Y18 (VSS75), U1.Y20 (VSS76), U10.2 (GND), U11.12 (GND), U11.25 (GND), U11.45 (GND), U11.59 (GND), U11.69 (EP); also elsewhere on the board
GNDA: C157.2, C158.2, R110.2, U1.N6 (VREF-), U1.R6 (VSSA), U1.T6 (VSSA1), U1.U6 (VSSA2); also elsewhere on the board
I2C4_SCL: U11.47 (SCK); also elsewhere on the board
I2C4_SDA: U11.48 (SDA); also elsewhere on the board
IPS: C90.2, C91.2, C96.1, C97.1, C106.1, C110.2, C113.2, C114.2, C116.2, C118.2, C119.2, C120.2, C125.2, C129.2, CHGLED1.2 (A), IPS1.1, L8.1, T1.4 (S), T1.8 (S1), U10.5 (IN), U11.4 (FLDOIN), U11.6 (VIN5), U11.11 (VIN6), U11.15 (DLDOIN), U11.19 (VIN1), U11.22 (VIN4), U11.32 (ALDOIN), U11.38 (VIN3), U11.39 (VIN2-1), U11.40 (VIN2-2), U11.55 (IPSOUT1-1), U11.56 (IPSOUT1-2), U11.66 (VIN_CHG), U11.67 (ELDOIN)
NRST: R99.1; also elsewhere on the board
unnamed: C86.2, D2.1 (K), FET2.2, R97.1
unnamed: C92.2, R99.2, R100.1, R102.2, U11.46 (PWROK)
unnamed: C93.2, R103.2, U11.60 (PWRON)
unnamed: C99.1, U11.29 (ALDO2)
unnamed: C101.1, U11.35 (GPIO0/LDO)
unnamed: C102.1, U11.34 (GPIO1/LDO)
unnamed: C94.1, C95.1, C107.1, L9.1, R109.1, T1.1 (D), T1.2 (D1), T1.5 (D2), T1.6 (D3), T1.7 (D4), U11.63 (LOADSENSEP)
unnamed: C109.2, U11.18 (SWOUT)
unnamed: C122.2, U11.16 (DLDO2)
unnamed: C126.2, U11.68 (ELDO1)
unnamed: C127.2, U11.1 (ELDO2)
unnamed: C128.2, U11.2 (ELDO3)
unnamed: C130.2, U11.3 (FLDO1)
unnamed: C131.2, U11.5 (FLDO2)
unnamed: C132.2, R112.2, U11.50 (VINT)
unnamed: C133.2, U11.33 (VREF)
unnamed: C158.1, U1.P6 (VREF+), VREF1.2
unnamed: C163.1, U1.AB17 (VDDA1V1_REG)
unnamed: C164.1, C165.1, U1.AB12 (VDDA1V8_REG), U1.B14 (VDDA1V8_DSI)
unnamed: C166.1, U1.A18 (VDD1V2_DSI_PHY), U1.B18 (VDD1V2_DSI_REG)
unnamed: CHGLED1.1 (K), R104.2
unnamed: D2.2 (A), L8.2, U10.1 (LX)
unnamed: L9.2, U11.65 (LX_CHG)
unnamed: L10.1, U11.21 (LX1)
unnamed: L11.1, U11.36 (LX3-1), U11.37 (LX3-2)
unnamed: L12.1, U11.23 (LX4)
unnamed: L13.1, U11.7 (LX5)
unnamed: PWRLED1.2 (A), R101.2
unnamed: PWRON1.2, R103.1
unnamed: R97.2, R98.1, U10.3 (FB)
unnamed: R102.1, RESET1.2
unnamed: R104.1, U11.53 (CHGLED)
unnamed: R105.1, U11.30 (TS)
unnamed: R106.1, U11.61 (IRQ)
unnamed: R107.1, U11.26 (DP)
unnamed: R108.1, U11.27 (DM)
unnamed: R113.1, U1.AA12 (BYPASS_REG1V8)
unnamed: T1.3 (G), U11.52 (N_BATDRV)
USB-OTG-DRV: U11.51 (N_VBUSEN); also elsewhere on the board
USB_OTG_FS_DM: R108.2; also elsewhere on the board
USB_OTG_FS_DP: R107.2; also elsewhere on the board
VBAT: C87.2, C107.2, LIPO_BAT1.1, R109.2, U11.64 (BATSENSEN)
VDD: C121.2, C147.1, C148.1, C149.1, C150.1, C151.1, C152.1, C153.1, C154.1, C155.1, C159.1, C160.1, C161.1, C162.1, R100.2, U1.A14 (VDD_DSI), U1.D18 (VDD_PLL2), U1.M6 (VDD_PLL), U1.M9 (VDD), U1.N5 (VDD_ANA), U1.N8 (VDD1), U1.N10 (VDD2), U1.P9 (VDD3), U1.P11 (VDD5), U1.R10 (VDD6), U1.R12 (VDD7), U1.T13 (VDD8), U1.U9 (VDD4(OTP)), U1.U12 (VDD9), U1.U14 (VDD10), U11.17 (DLDO1), VDD1.1; also elsewhere on the board
VDDA: C98.1, C157.1, U1.R5 (VDDA), U11.28 (ALDO1), VDDA1.1, VREF1.1
VDD_USB: C100.1, C167.1, U1.AB13 (VDD3V3_USBHS), U1.AB16 (VDD3V3_USBFS), U11.31 (ALDO3), VDD_USB1.1
VTT_DDR: C115.2, L12.2, U11.24 (DCDC4); also elsewhere on the board

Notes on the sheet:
Power Supply
Vout=0.6*(1+Ra/Rb)
LI-ION_BATTERY 4.2V
+5VDC ONLY!!!
DC5SET DDR3-VCC Floating 1.24V GND 1.50V VINT 1.36V
3.3V
VDDCORE 1.2V
Vtt_DDR 0.675V
VDDDDR 1.35V
VDD(IO)
1.8V EMMC
2.8V
VDDA
VDD3.3V_USB
